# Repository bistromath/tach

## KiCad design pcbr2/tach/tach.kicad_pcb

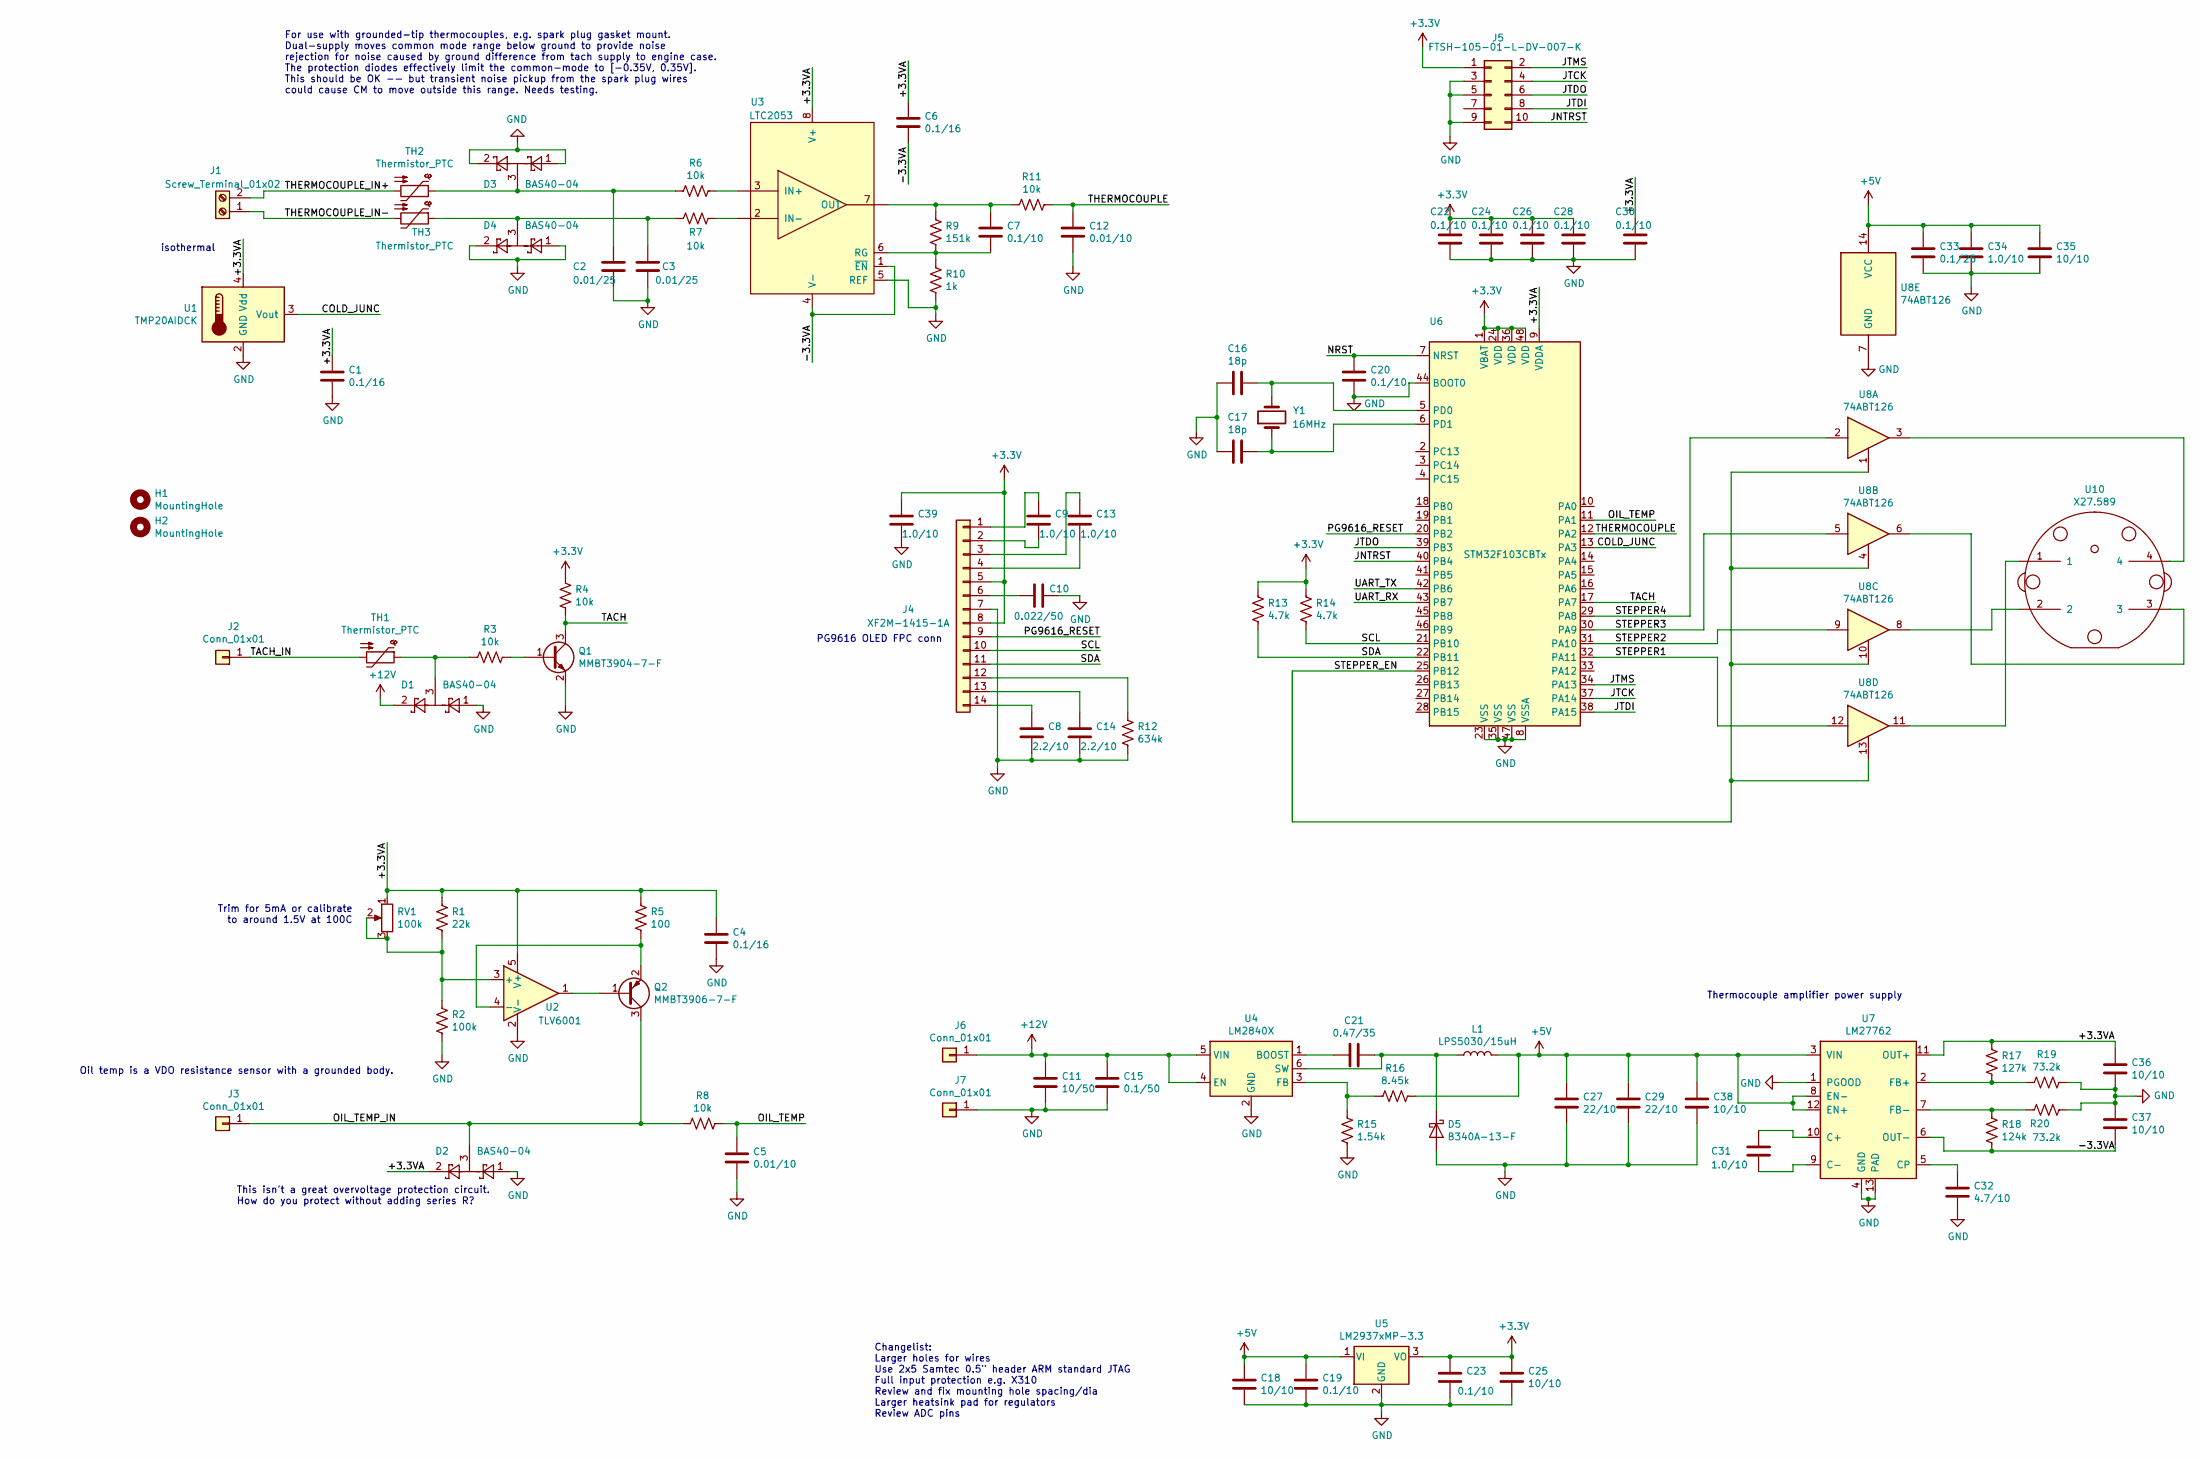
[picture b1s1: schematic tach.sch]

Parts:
C1, C4, C6: 0.1/16; C_0402
C2, C3: 0.01/25; C_0402
C5, C12: 0.01/10; C_0402
C7, C19, C20, C22, C23, C24, C26, C28, C30: 0.1/10; C_0402
C8, C14: 2.2/10; C_0402
C9, C13, C31, C39: 1.0/10; C_0402
C10: 0.022/50; C_0402
C11: 10/50; C_1206
C15: 0.1/50; C_0402
C16, C17: 18p; C_0402
C18, C25, C35, C38: 10/10; C_0805
C21: 0.47/35; C_0603
C27, C29: 22/10; C_0805
C32: 4.7/10; C_0603
C33: 0.1/25; C_0402
C34: 1.0/10; C_0805
C36, C37: 10/10; C_0402
D1, D2, D3, D4: BAS40-04; SOT-23
D5: B340A-13-F; D_SMA
H1, H2: MountingHole; MountingHole_2.5mm
J1: Screw_Terminal_01x02; TerminalBlock_bornier-2_P5.08mm
J2, J3, J6, J7: Conn_01x01; mountinghole-1.5mm
J4: XF2M-1415-1A
J5: FTSH-105-01-L-DV-007-K
L1: LPS5030/15uH; MSS6132T
Q1: MMBT3904-7-F; SOT-23
Q2: MMBT3906-7-F; SOT-23
R1: 22k; R_0402
R2: 100k; R_0402
R3, R4, R6, R7, R8, R11: 10k; R_0402
R5: 100; R_0402
R9: 151k; R_0402
R10: 1k; R_0402
R12: 634k; R_0402
R13, R14: 4.7k; R_0402
R15: 1.54k; R_0402
R16: 8.45k; R_0402
R17: 127k; R_0402
R18: 124k; R_0402
R19, R20: 73.2k; R_0402
RV1: 100k; Potentiometer_Trimmer_Bourns_3224J
TH1, TH2, TH3: Thermistor_PTC; R_0603
U1: TMP20AIDCK; SOT-353_SC-70-5
U2: TLV6001; TSOT-23-5
U3: LTC2053; MSOP-8_3x3mm_Pitch0.65mm
U4: LM2840X; TSOT-23-6
U5: LM2937xMP-3.3; SOT-223-3_TabPin2
U6: STM32F103CBTx; LQFP-48_7x7mm_Pitch0.5mm
U7: LM27762; WSON-12-1EP_3x2mm_Pitch0.5mm_ThermalVias
U8: 74ABT126; TSSOP-14_4.4x5mm_Pitch0.65mm
U10: X27.589
Y1: 16MHz; Crystal_SMD_TXC_7M-4pin_3.2x2.5mm

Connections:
+3V3: C22.1, C23.1, C24.1, C25.1, C26.1, C28.1, C39.1, J4.5, J4.8, J5.1, R4.1, R13.1, R14.1, U5.3 (VO), U6.1 (VBAT), U6.24 (VDD), U6.36 (VDD), U6.48 (VDD)
+5V: C18.1, C19.1, C27.1, C29.1, C33.1, C34.1, C35.1, C38.1, L1.2, R16.1, U5.1 (VI), U7.3 (VIN), U7.8 (EN-), U7.12 (EN+), U8.14 (VCC)
+12V: C11.1, C15.1, D1.2, J6.1, U4.4 (EN), U4.5 (VIN)
/+3.3VA: C1.1, C4.1, C6.1, C30.1, C36.1, D2.2, R1.1, R5.1, R17.1, RV1.1, U1.4 (Vdd), U2.5 (V+), U3.8 (V+), U6.9 (VDDA), U7.11 (OUT+)
/-3.3VA: C6.2, C37.2, R18.2, U3.1 (~EN), U3.4 (V-), U7.6 (OUT-)
/COLD_JUNC: U1.3 (Vout), U6.13 (PA3)
/JNTRST: J5.10, U6.40 (PB4)
/JTCK: J5.4, U6.37 (PA14)
/JTDI: J5.8, U6.38 (PA15)
/JTDO: J5.6, U6.39 (PB3)
/JTMS: J5.2, U6.34 (PA13)
/NRST: C20.1, U6.7 (NRST)
/OIL_TEMP: C5.1, R8.1, U6.11 (PA1)
/OIL_TEMP_IN: D2.3, J3.1, Q2.3 (C), R8.2
/PG9616_RESET: J4.9, U6.20 (PB2)
/SCL: J4.10, R14.2, U6.21 (PB10)
/SDA: J4.11, R13.2, U6.22 (PB11)
/STEPPER1: U6.32 (PA11), U8.12
/STEPPER2: U6.31 (PA10), U8.9
/STEPPER3: U6.30 (PA9), U8.5
/STEPPER4: U6.29 (PA8), U8.2
/STEPPER_EN: U6.25 (PB12), U8.1, U8.4, U8.10, U8.13
/TACH: Q1.3 (C), R4.2, U6.17 (PA7)
/TACH_IN: J2.1, TH1.2
/THERMOCOUPLE: C12.1, R11.1, U6.12 (PA2)
/THERMOCOUPLE_IN+: J1.2, TH2.2
/THERMOCOUPLE_IN-: J1.1, TH3.2
/UART_RX: U6.43 (PB7)
/UART_TX: U6.42 (PB6)
GND: C1.2, C2.2, C3.2, C4.2, C5.2, C8.2, C10.1, C11.2, C12.2, C14.2, C15.2, C16.2, C17.2, C18.2, C19.2, C20.2, C22.2, C23.2, C24.2, C25.2, C26.2, C27.2, C28.2, C29.2, C30.2, C32.2, C33.2, C34.2, C35.2, C36.2, C37.1, C38.2, C39.2, D1.1, D2.1, D3.1, D3.2, D4.1, D4.2, D5.2 (A), J4.7, J5.3, J5.5, J5.9, J7.1, Q1.2 (E), R2.2, R10.2, R12.1, R15.2, R19.1, R20.1, U1.2 (GND), U1.5 (GND), U2.2 (V-), U3.5 (REF), U4.2 (GND), U5.2 (GND), U6.8 (VSSA), U6.23 (VSS), U6.35 (VSS), U6.44 (BOOT0), U6.47 (VSS), U7.1 (PGOOD), U7.4 (GND), U7.13 (PAD), U8.7 (GND)
unnamed: C2.1, D3.3, R6.2, TH2.1
unnamed: C3.1, D4.3, R7.2, TH3.1
unnamed: C7.1, R9.1, R11.2, U3.7 (OUT)
unnamed: C7.2, R9.2, R10.1, U3.6 (RG)
unnamed: C8.1, J4.14
unnamed: C9.1, J4.1
unnamed: C9.2, J4.2
unnamed: C10.2, J4.6
unnamed: C13.1, J4.3
unnamed: C13.2, J4.4
unnamed: C14.1, J4.13
unnamed: C16.1, U6.5 (PD0), Y1.2
unnamed: C17.1, U6.6 (PD1), Y1.1
unnamed: C21.1, D5.1 (K), L1.1, U4.6 (SW)
unnamed: C21.2, U4.1 (BOOST)
unnamed: C31.1, U7.10 (C+)
unnamed: C31.2, U7.9 (C-)
unnamed: C32.1, U7.5 (CP)
unnamed: D1.3, R3.2, TH1.1
unnamed: J4.12, R12.2
unnamed: Q1.1 (B), R3.1
unnamed: Q2.1 (B), U2.1
unnamed: Q2.2 (E), R5.2, U2.4 (-)
unnamed: R1.2, R2.1, RV1.2, RV1.3, U2.3 (+)
unnamed: R6.1, U3.3 (IN+)
unnamed: R7.1, U3.2 (IN-)
unnamed: R15.1, R16.2, U4.3 (FB)
unnamed: R17.2, R19.2, U7.2 (FB+)
unnamed: R18.1, R20.2, U7.7 (FB-)
unnamed: U8.11, U10.1
unnamed: U8.8, U10.2
unnamed: U8.6, U10.3
unnamed: U8.3, U10.4

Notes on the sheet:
Changelist: Larger holes for wires Use 2x5 Samtec 0.5" header ARM standard JTAG Full input protection e.g. X310 Review and fix mounting hole spacing/dia Larger heatsink pad for regulators Review ADC pins
For use with grounded-tip thermocouples, e.g. spark plug gasket mount. Dual-supply moves common mode range below ground to provide noise rejection for noise caused by ground difference from tach supply to engine case. The protection diodes effectively limit the common-mode to [-0.35V, 0.35V]. This 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
Trim for 5mA or calibrate to around 1.5V at 100C
This isn't a great overvoltage protection circuit. How do you protect without adding series R?
Thermocouple amplifier power supply
PG9616 OLED FPC conn
isothermal
Oil temp is a VDO resistance sensor with a grounded body.

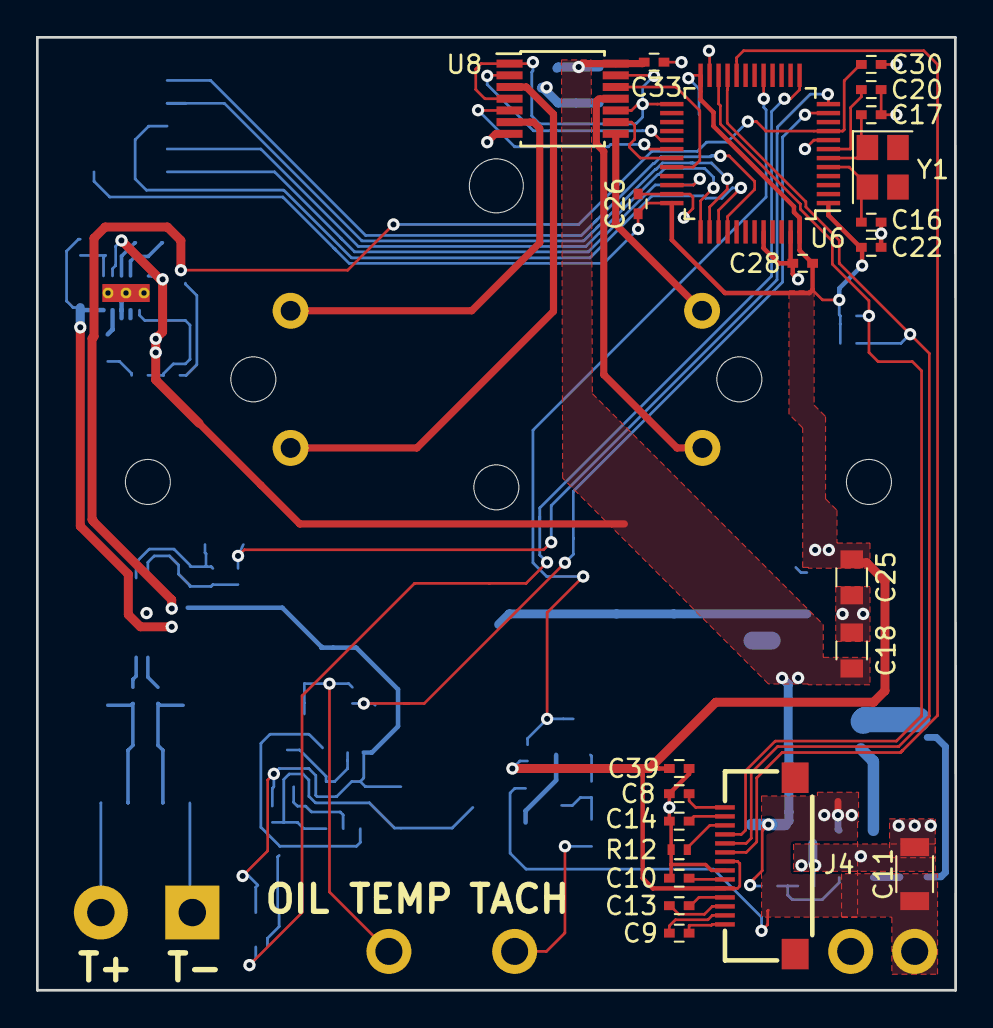
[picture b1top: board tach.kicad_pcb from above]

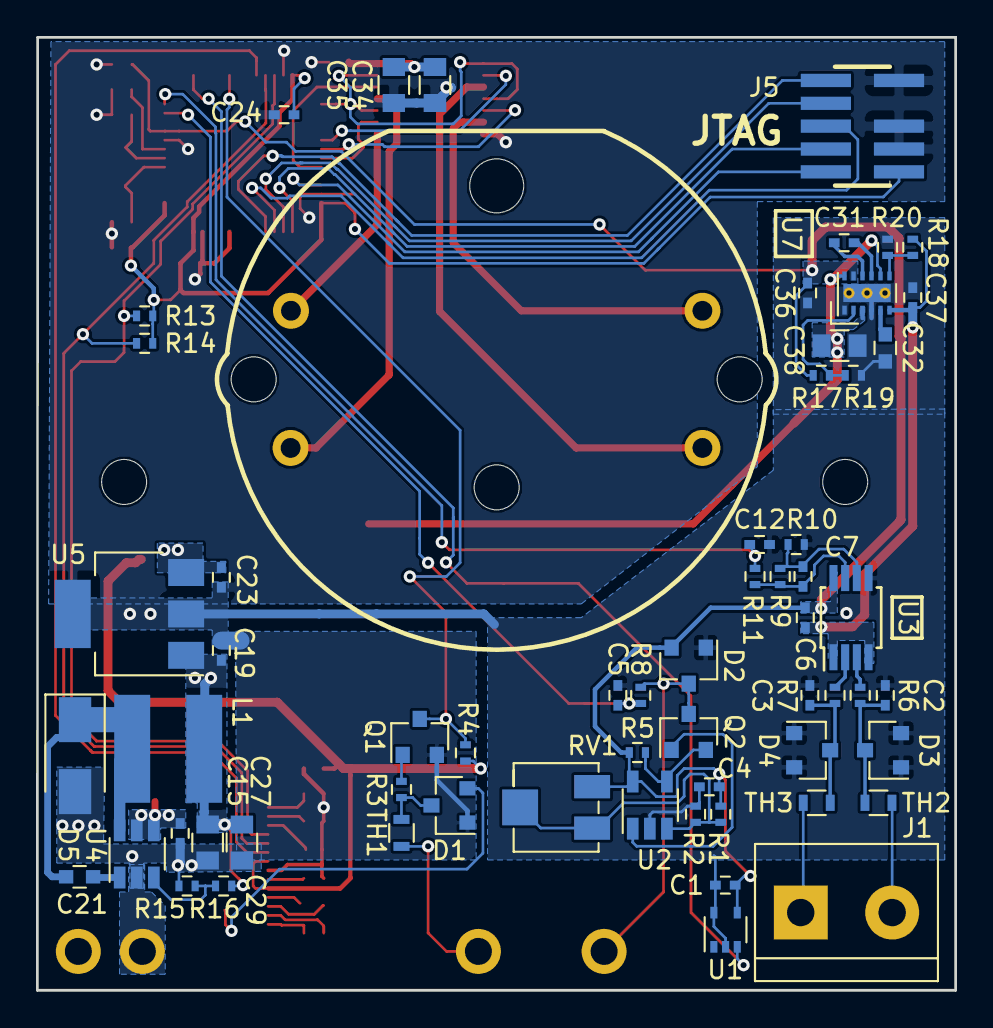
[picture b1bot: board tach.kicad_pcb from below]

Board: 2 copper layers, 51.0 x 52.9 mm, 90 parts (62 on the bottom side), 61 nets.

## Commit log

2014-08-29 Initial commit. Backed off main clock to 16MHz to save power (heat in 3.3Vreg)
2014-08-29 Fix display bug, move ADC to divisor 1.
2020-04-07 Huge bulk commit with working rev 2 PCB and files. Some errata, but tested working.
2020-04-07 Back to production display.
2025-07-13 this commit preserves the state of the repo as of 7/13/26. confirmed working in hardware.
